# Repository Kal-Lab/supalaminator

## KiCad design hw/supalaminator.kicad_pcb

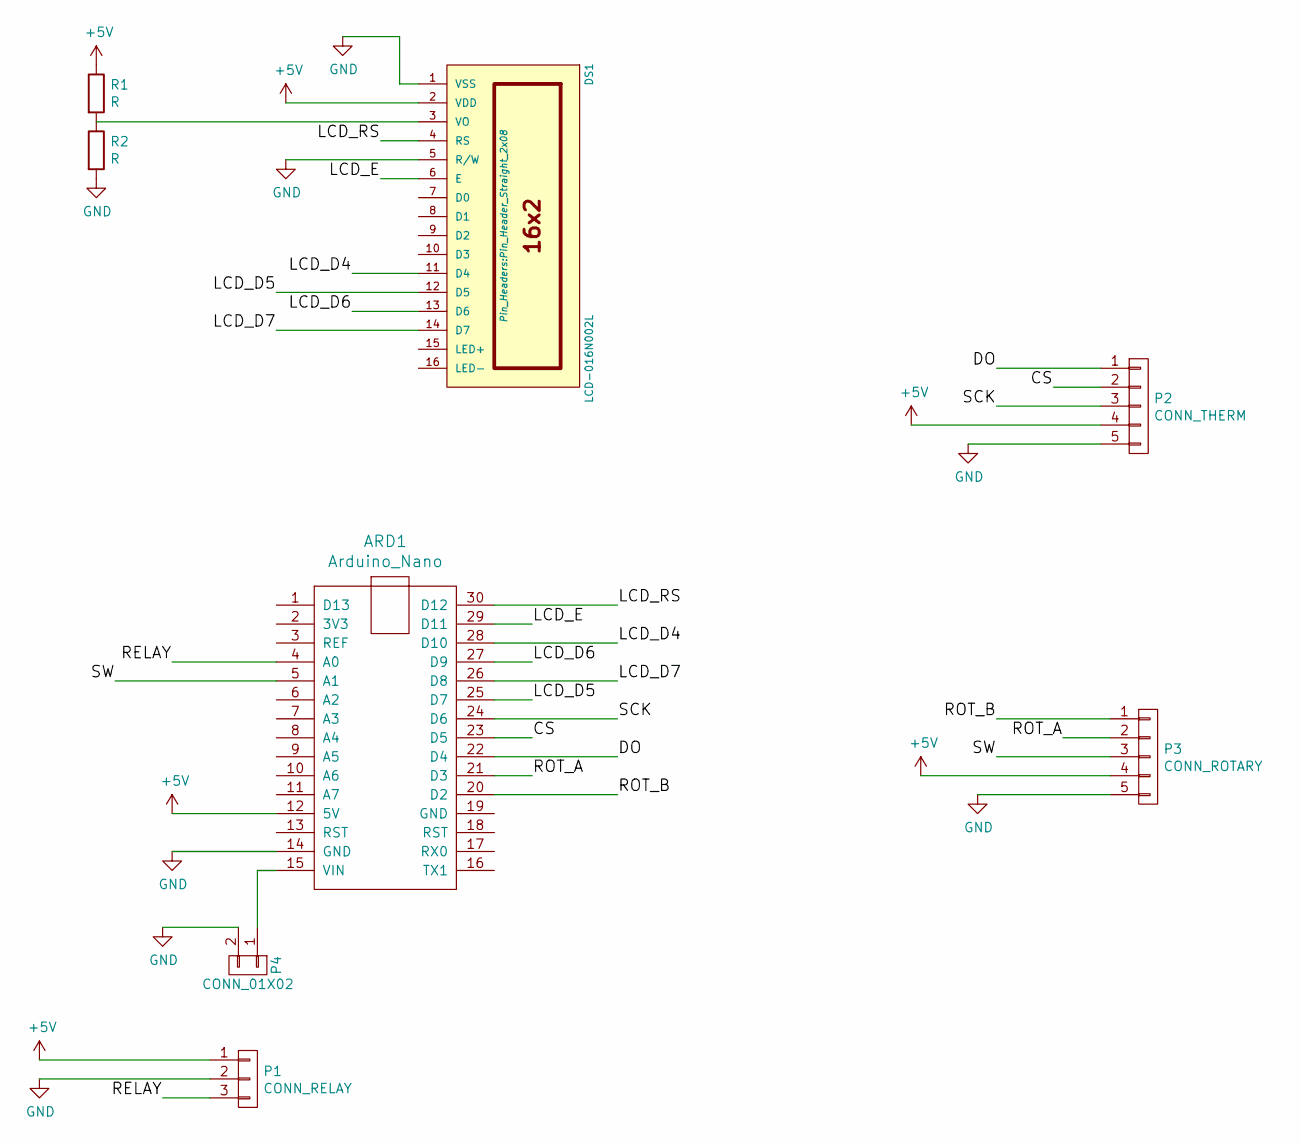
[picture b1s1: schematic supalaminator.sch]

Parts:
ARD1: Arduino_Nano; Arduino Nano
DS1: LCD-016N002L; Pin_Header_Straight_2x08
P1: CONN_RELAY; Pin_Header_Straight_1x03
P2: CONN_THERM; Pin_Header_Straight_1x05
P3: CONN_ROTARY; Pin_Header_Straight_1x05
P4: CONN_01X02; Pin_Header_Straight_1x02
R1, R2: R; Resistor_Horizontal_RM7mm

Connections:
+5V: ARD1.12 (5V), DS1.2 (VDD), P1.1, P2.4, P3.4, R1.1
/CS: ARD1.23 (D5), P2.2
/DO: ARD1.22 (D4), P2.1
/LCD_D4: ARD1.28 (D10), DS1.11 (D4)
/LCD_D5: ARD1.25 (D7), DS1.12 (D5)
/LCD_D6: ARD1.27 (D9), DS1.13 (D6)
/LCD_D7: ARD1.26 (D8), DS1.14 (D7)
/LCD_E: ARD1.29 (D11), DS1.6 (E)
/LCD_RS: ARD1.30 (D12), DS1.4 (RS)
/RELAY: ARD1.4 (A0), P1.3
/ROT_A: ARD1.21 (D3), P3.2
/ROT_B: ARD1.20 (D2), P3.1
/SCK: ARD1.24 (D6), P2.3
/SW: ARD1.5 (A1), P3.3
GND: ARD1.14 (GND), DS1.1 (VSS), DS1.5 (R/W), P1.2, P2.5, P3.5, P4.2, R2.2
unnamed: ARD1.15 (VIN), P4.1
unnamed: DS1.3 (VO), R1.2, R2.1

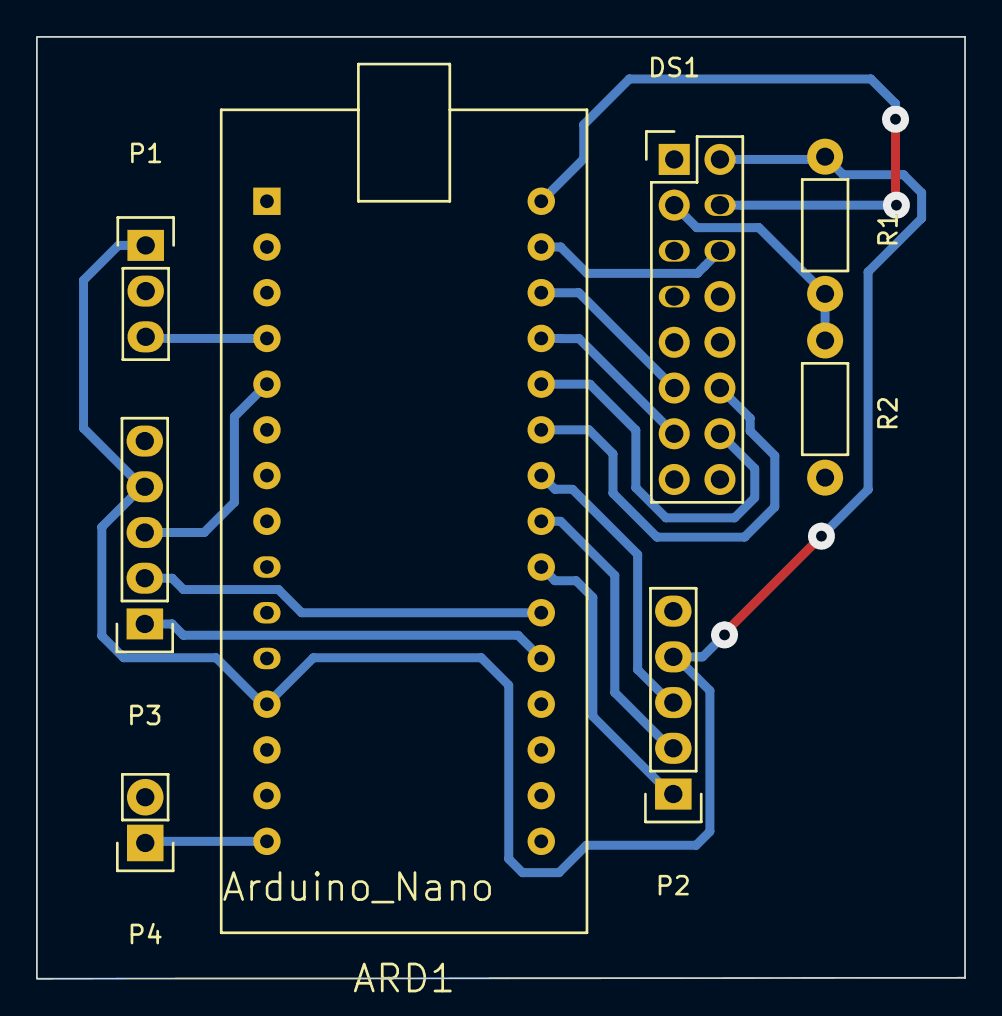
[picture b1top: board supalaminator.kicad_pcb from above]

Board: 2 copper layers, 51.6 x 52.3 mm, 8 parts (0 on the bottom side), 17 nets.

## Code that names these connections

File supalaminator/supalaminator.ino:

// this example is public domain. enjoy!
// www.ladyada.net/learn/sensors/thermocouple

#include <LiquidCrystal.h>
#include <max6675.h>
#include <Encoder.h>

/* Rotary Encoder */
#define ENC_A_PIN 2
#define ENC_B_PIN 3
#define ENC_SW_PIN A1

/* Relay */
#define RELAY_PIN A0

/* THERMAL */
#define THERM_DO 4
#define THERM_CS 5
#define THERM_CLK  6

/* LCD */
#define LCD_RS_PIN 12
#define LCD_EN_PIN 11
#define LCD_D4_PIN  10
#define LCD_D5_PIN  7
#define LCD_D6_PIN  9
#define LCD_D7_PIN  8


#define THRESHOLD      1
#define MAX_TEMP       160
#define MIN_TEMP       100

#define DEFAULT_TEMP   120

byte heat_char[8] = {
  0b00000,
  0b00100,
  0b01110,
  0b10101,
  0b00100,
  0b00100,
  0b00100,
  0b00100
};

byte heat_invert_char[8] = {
  0b11111,
  0b11011,
  0b10001,
  0b01010,
  0b11011,
  0b11011,
  0b11011,
  0b11011
};

byte degree_char[8] = {
  0b00000,
  0b11000,
  0b11000,
  0b00011,
  0b00100,
  0b00100,
  0b00100,
  0b00011
};


#define HEAT_CHAR 0
#define HEAT_INVERT_CHAR 1
#define DEGREE_CHAR 2

#define STATE_SET_MIN_TEMP 0
#define STATE_SET_MAX_TEMP 1
#define STATE_IDLE 2
#define STATE_COUNT 3

#define HEATING_ON 0
#define HEATING_OFF 1

#define LCD_UPDATE  200
#define CHAR_UPDATE  500

MAX6675 thermocouple(THERM_CLK, THERM_CS, THERM_DO);
Encoder enc(ENC_A_PIN, ENC_B_PIN);
// initialize the library with the numbers of the interface pins
LiquidCrystal lcd(LCD_RS_PIN, LCD_EN_PIN, LCD_D4_PIN, LCD_D5_PIN, LCD_D6_PIN, LCD_D7_PIN);

float ref_temp = DEFAULT_TEMP;

unsigned long last_millis = 0;
unsigned int heat_state = HEATING_OFF;

long last_enc_pos;

static void 
lcd_draw_ref_temp()
{
  lcd.setCursor(0,0);

  lcd.print("Ref:  ");
  lcd.print(ref_temp);
  lcd.write((uint8_t)DEGREE_CHAR);
  lcd.print("  ");

  Serial.print("New reference temp: ");
  Serial.println(ref_temp);
}

void setup() {
  Serial.begin(9600);
  Serial.println("Starting thermal control");

  lcd.begin(16, 2);
  lcd.createChar(HEAT_CHAR, heat_char);
  lcd.createChar(HEAT_INVERT_CHAR, heat_invert_char);
  lcd.createChar(DEGREE_CHAR, degree_char);

  lcd_draw_ref_temp();
  
  pinMode(ENC_SW_PIN, INPUT_PULLUP);
  pinMode(RELAY_PIN, OUTPUT);
  /* Disable relay */
  digitalWrite(RELAY_PIN, 1);
  last_enc_pos = enc.read();

  // wait for MAX chip to stabilize
  delay(500);
}


unsigned long heat_char_update = 0;
int heat_char_idx = HEAT_CHAR;

static void
draw_lcd(float cur_temp)
{
  /* Current temp */
  lcd.setCursor(0, 1);
  lcd.print("Temp: ");
  lcd.print(cur_temp);
  lcd.write((uint8_t)DEGREE_CHAR);
  lcd.print(" ");

  Serial.print("Temp:");
  Serial.println(cur_temp);

  if (heat_state == HEATING_ON) {
    if (millis() - heat_char_update > CHAR_UPDATE)  {
      if (heat_char_idx == HEAT_CHAR)
        heat_char_idx = HEAT_INVERT_CHAR;
      else 
        heat_char_idx = HEAT_CHAR;
        heat_char_update = millis();
    }
    lcd.write((uint8_t) heat_char_idx);
  }
  lcd.print("  ");
  last_millis = millis();
}


int get_enc_dir()
{
  long new_pos = enc.read();
  int dir = 0;

  if (new_pos < last_enc_pos)
    dir = -1;
  else if (new_pos > last_enc_pos)
    dir = 1;

  last_enc_pos = new_pos;
  delay(50);
  return dir;
}


static void
set_ref_temp()
{
  int dir = get_enc_dir();
  if (dir) {
    ref_temp += dir;
    if (ref_temp > MAX_TEMP)
      ref_temp = MAX_TEMP;
    if (ref_temp < MIN_TEMP)
      ref_temp = MIN_TEMP;

    lcd_draw_ref_temp();
  }
}

unsigned long last_heating = 0;

static void
manage_heating(float temp)
{
    switch(heat_state) {
    case HEATING_ON:
      if (temp >= (ref_temp + THRESHOLD)) {
        heat_state = HEATING_OFF;
        digitalWrite(RELAY_PIN, 1);
        Serial.println("Heating Off !");
      }
      break;
    case HEATING_OFF:
      if (temp <= ref_temp) {
        heat_state = HEATING_ON;
        digitalWrite(RELAY_PIN, 0);
        Serial.println("Heating On !");
      }
      break;
  }
}

unsigned long temp_milli = 0;

void loop()
{
  if (millis() - temp_milli > 300) {
	  float temp = thermocouple.readCelsius();
	  draw_lcd(temp);
	  manage_heating(temp);
    temp_milli = millis();
  }
  
  set_ref_temp();
}

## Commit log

2016-07-23 Supalaminator: first files
2016-07-25 Update arduino sketch
2016-07-25 Add hardware
2016-07-25 Final hardware schematic
2016-08-09 Add power source
2016-08-09 Ino: fix wrong lcd init and lcd drawing
